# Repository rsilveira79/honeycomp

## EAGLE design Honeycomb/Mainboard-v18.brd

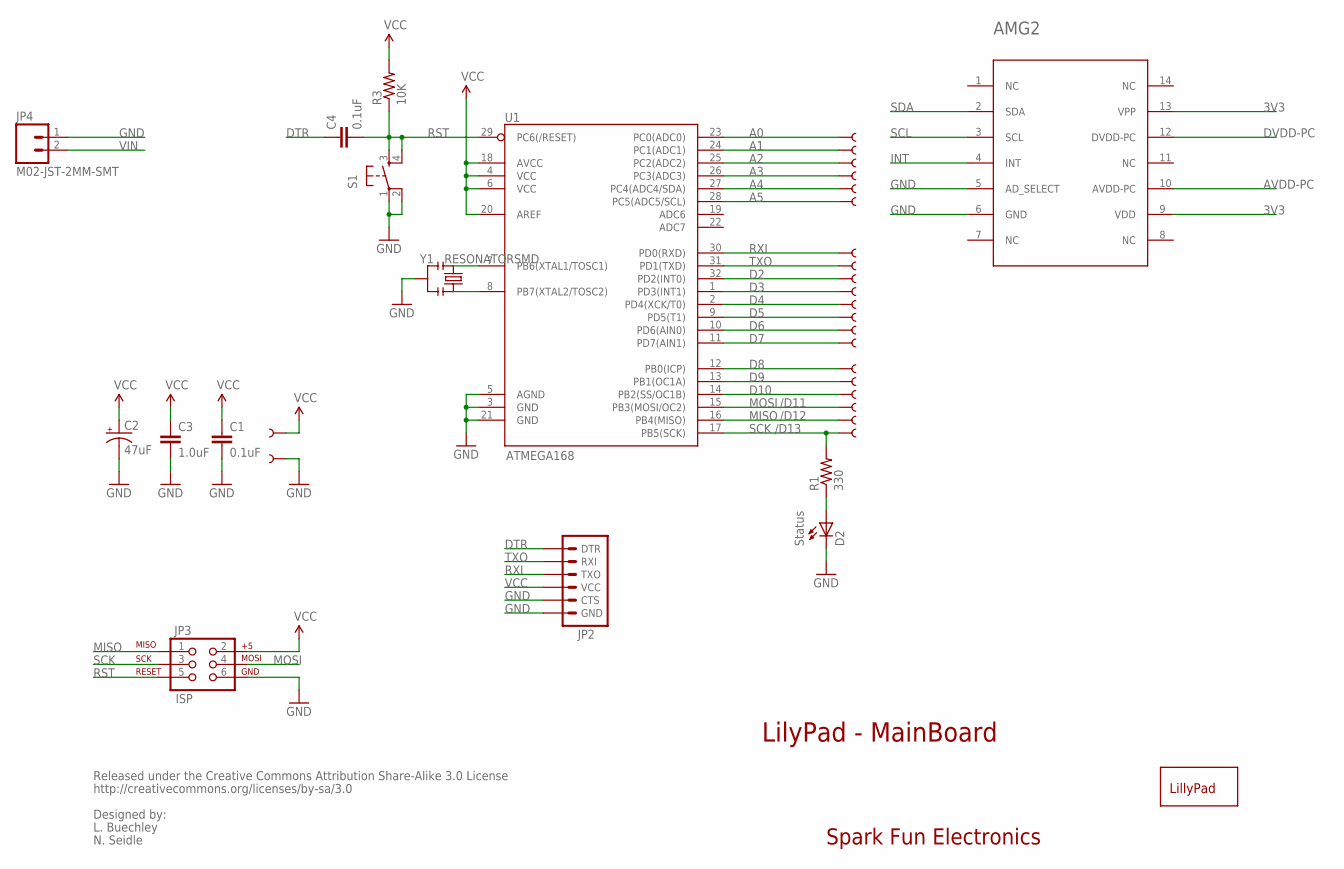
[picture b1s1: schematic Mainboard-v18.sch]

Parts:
AMG2: AMG8831
C1, C4: 0.1uF; 0603
C2: 47uF; EIA3528
C3: 1.0uF; 0603
D2: Status; LED-0603
GND: SEWTAP1; SEWTAP
JP2: ARDUINO_SERIAL_PROGRAMSMD; 1X06-SMD
JP3: ISP; 2X3-NS
JP4: M02-JST-2MM-SMT; JST-2-SMD
R1: 330; 0603
R3: 10K; 0603
S1: TAC_SWITCHSMD; TACTILE_SWITCH_SMD
U1: ATMEGA168; TQFP32-08
U$1: LOGO-LPLPA; LOGO-LPA
U$4, U$30, U$31, U$32, U$33, U$34, U$35, U$36, U$37, U$38, U$39, U$40, U$41, U$42, U$43, U$44, U$45, U$46, U$47, U$48, U$51: SEWTAP1; SEWTAP
Y1: RESONATORSMD; RESONATOR-SMD

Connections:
3V3: AMG2.9 (VDD), AMG2.13 (VPP)
A0: U1.23 (PC0(ADC0)), U$4.1
A1: U1.24 (PC1(ADC1)), U$30.1
A2: U1.25 (PC2(ADC2)), U$31.1
A3: U1.26 (PC3(ADC3)), U$32.1
A4: U1.27 (PC4(ADC4/SDA)), U$33.1
A5: U1.28 (PC5(ADC5/SCL)), U$34.1
AVDD-PC: AMG2.10 (AVDD-PC)
D2: U1.32 (PD2(INT0)), U$45.1
D3: U1.1 (PD3(INT1)), U$44.1
D4: U1.2 (PD4(XCK/T0)), U$43.1
D5: U1.9 (PD5(T1)), U$42.1
D6: U1.10 (PD6(AIN0)), U$41.1
D7: U1.11 (PD7(AIN1)), U$48.1
D8: U1.12 (PB0(ICP)), U$35.1
D9: U1.13 (PB1(OC1A)), U$36.1
D10: U1.14 (PB2(SS/OC1B)), U$37.1
DTR: C4.1, JP2.1 (DTR)
DVDD-PC: AMG2.12 (DVDD-PC)
GND: AMG2.5 (AD_SELECT), AMG2.6 (GND), C1.2, C2.C (-), C3.2, D2.C, GND.1, JP2.5 (CTS), JP2.6 (GND), JP3.6, JP4.1 (2), S1.1, S1.2, U1.3 (GND), U1.5 (AGND), U1.21 (GND), Y1.2
INT: AMG2.4 (INT)
MISO: JP3.1, U1.16 (PB4(MISO)), U$39.1
MOSI: JP3.4, U1.15 (PB3(MOSI/OC2)), U$38.1
unnamed: U1.7 (PB6(XTAL1/TOSC1)), Y1.1
unnamed: D2.A, R1.1
unnamed: U1.8 (PB7(XTAL2/TOSC2)), Y1.3
RST: C4.2, JP3.5, R3.1, S1.3, S1.4, U1.29 (PC6(/RESET))
RXI: JP2.3 (TXO), U1.30 (PD0(RXD)), U$47.1
SCK: JP3.3, R1.2, U1.17 (PB5(SCK)), U$40.1
SCL: AMG2.3 (SCL)
SDA: AMG2.2 (SDA)
TXO: JP2.2 (RXI), U1.31 (PD1(TXD)), U$46.1
VCC: C1.1, C2.A (+), C3.1, JP2.4 (VCC), JP3.2, R3.2, U1.4 (VCC), U1.6 (VCC), U1.18 (AVCC), U1.20 (AREF), U$51.1
VIN: JP4.2 (1)

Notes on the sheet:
LilyPad - MainBoard
Spark Fun Electronics
/D11
/D12
/D13
Released under the Creative Commons Attribution Share-Alike 3.0 License
http://creativecommons.org/licenses/by-sa/3.0
Designed by:
L. Buechley
N. Seidle

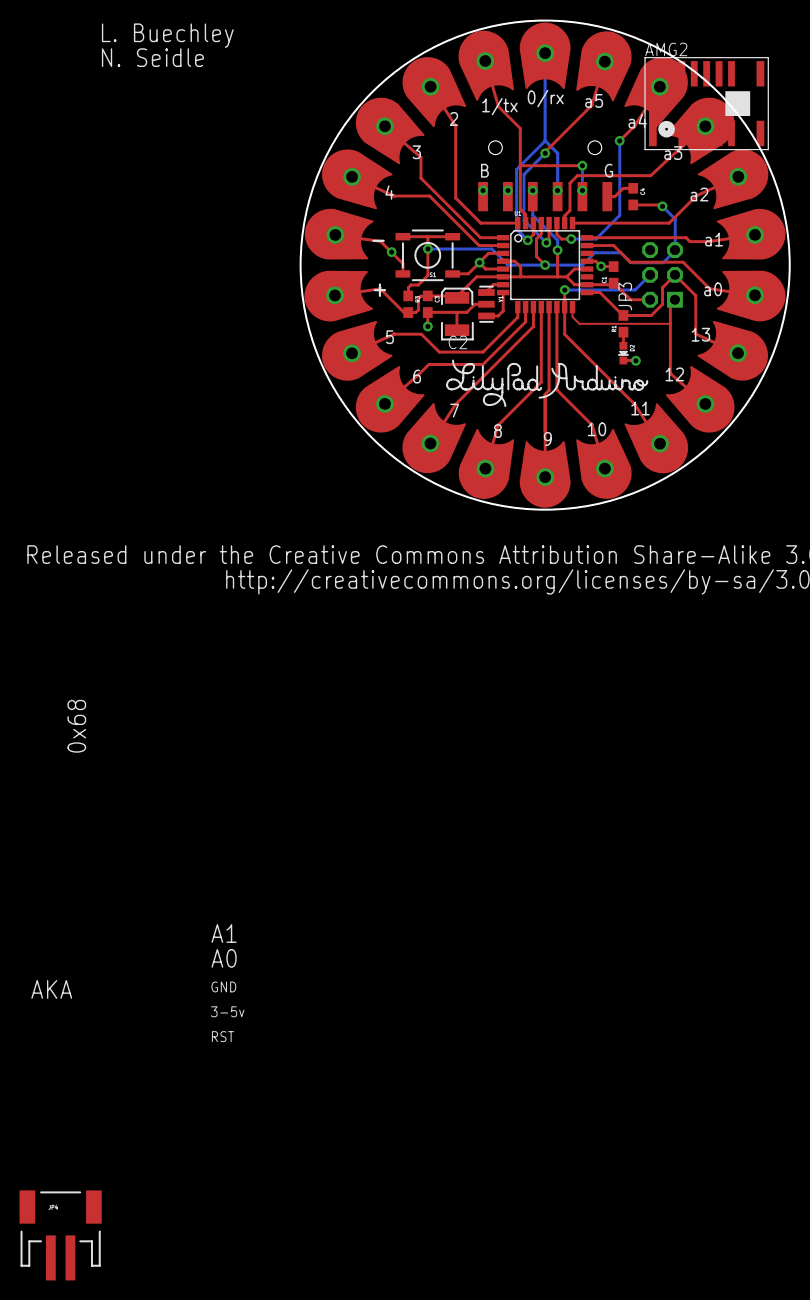
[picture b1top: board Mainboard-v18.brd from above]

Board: 2 copper layers, 50.0 x 50.0 mm, 37 parts (0 on the bottom side), 28 nets.

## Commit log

2016-03-02 First commit Honeycomb

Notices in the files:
parts and their libraries:
SparkFun-Connectors: Licensing: CC v3.0 Share-Alike You are welcome to use this library for commercial purposes.
